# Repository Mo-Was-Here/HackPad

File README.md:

# 🚀 My Custom 3-Key Hackpad

> ⚠️ **Development Note:** The current 3D enclosure base file (`Top.STL`) is an initial layout draft to fulfill the folder architecture requirements. It is not currently matched to the exact final physical dimensions of the routed PCB and will be updated with precise mechanical alignments before final hardware fabrication.

A custom 3-key mechanical macro keypad featuring an integrated rotary encoder dial and individually addressable RGB backlight LEDs. The entire hardware framework is driven by a Seeed Studio XIAO RP2040 microcontroller and runs on the Python-based KMK keyboard firmware framework.

---

## 📐 Project Structure

This repository contains all source and manufacturing files required to build this project, organized according to Hack Club's shipping guidelines:
* `/CAD` - Contains the structural 3D design file (Top.STL) for the switch plate enclosure.
* `/PCB` - Contains the editable KiCad project, schematic, and board layout files.
* `/firmware` - Contains the core KMK configuration script (main.py).
* `/production` - Contains the manufacturing-ready gerbers.zip bundle and configuration assets.

---

## 📋 Bill of Materials (BOM)

| Component | Description | Qty | Part Source Link |
| :--- | :--- | :---: | :--- |
| **MCU** | Seeed Studio XIAO RP2040 Module | 1 | [Seeed Studio Official](https://seeedstudio.com) |
| **Switches** | Cherry MX Mechanical Keyswitches | 3 | [DigiKey Catalog](https://digikey.com) |
| **Encoder** | EC11 Rotary Encoder Dial with Built-in Switch | 1 | [Adafruit Supply](https://adafruit.com) |
| **LEDs** | SK6812MINI-E Individual Addressable RGB Components | 2 | [JLCPCB Parts Library](https://jlcpcb.com) |
| **Enclosure** | 1.5mm Custom 3D-Printed Switch Plate Base Shell | 1 | *Custom Manufactured STL File* |

---

## 🛠️ Pinout Mapping Reference

*   **SW1 (Key 1)** $\rightarrow$ GPIO Pin 11 (`board.D10`)
*   **SW2 (Key 2)** $\rightarrow$ GPIO Pin 10 (`board.D9`)
*   **SW3 (Key 3)** $\rightarrow$ GPIO Pin 9 (`board.D8`)
*   **Rotary Encoder Pins** $\rightarrow$ A: Pin 1 (`board.D0`) / B: Pin 2 (`board.D1`) / Switch: Pin 3 (`board.D2`)
*   **NeoPixel Data Bus** $\rightarrow$ Pin 7 (`board.D6`)
*   **Common Rails** $\rightarrow$ Positive: `+3V3` / Negative Return Path: `GND`

---

## 💻 Firmware Setup Instructions
This board runs CircuitPython with the KMK framework library. To deploy:
1. Flash the Seeed Studio XIAO with the latest CircuitPython .UF2 payload.
2. Copy the `kmk` firmware directory onto the root directory of the microcontroller storage volume.
3. Move the provided `main.py` configuration script onto the board to instantly map keybinds and lighting profiles.

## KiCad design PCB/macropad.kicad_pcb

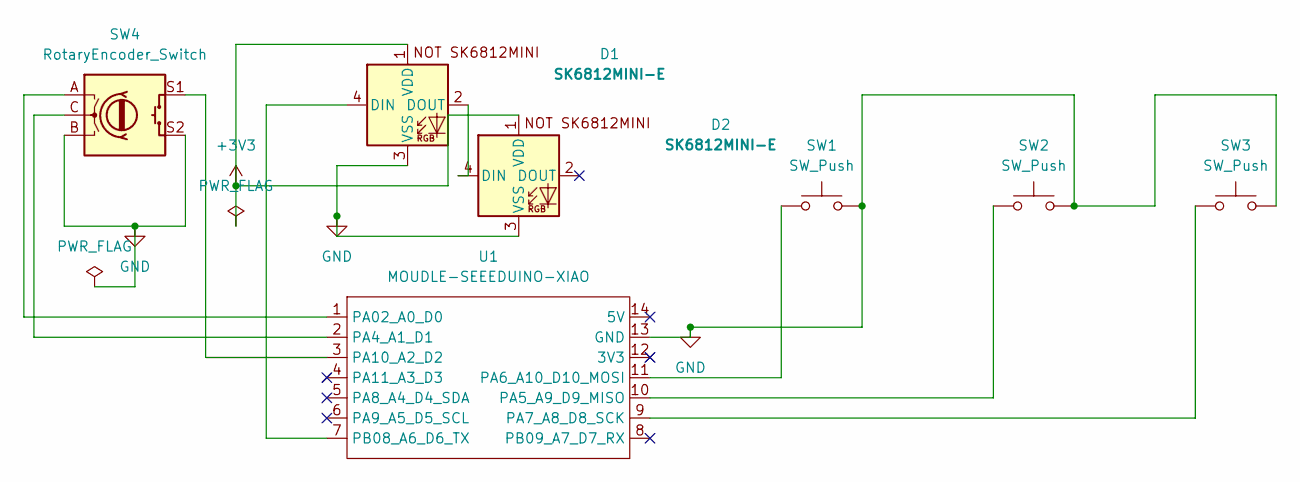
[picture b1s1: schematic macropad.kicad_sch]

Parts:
D1, D2: SK6812MINI-E; SK6812MINI-E_fixed
SW1, SW2, SW3: SW_Push; SW_Cherry_MX_1.25u_PCB
SW4: RotaryEncoder_Switch; RotaryEncoder_Alps_EC11E-Switch_Vertical_H20mm
U1: MOUDLE-SEEEDUINO-XIAO; MCU_Seeed_ESP32C3

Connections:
+3V3: D1.1 (VDD), D2.1 (VDD)
GND: D1.3 (VSS), D2.3 (VSS), SW1.2, SW2.2, SW3.2, SW4.B, SW4.S2, U1.13 (GND)
unnamed: D1.4 (DIN), U1.7 (PB08_A6_D6_TX)
unnamed: D1.2 (DOUT), D2.4 (DIN)
unnamed: SW4.A, U1.1 (PA02_A0_D0)
unnamed: SW4.C, U1.2 (PA4_A1_D1)
unnamed: SW2.1, U1.10 (PA5_A9_D9_MISO)
unnamed: SW1.1, U1.11 (PA6_A10_D10_MOSI)
unnamed: SW3.1, U1.9 (PA7_A8_D8_SCK)
unnamed: SW4.S1, U1.3 (PA10_A2_D2)

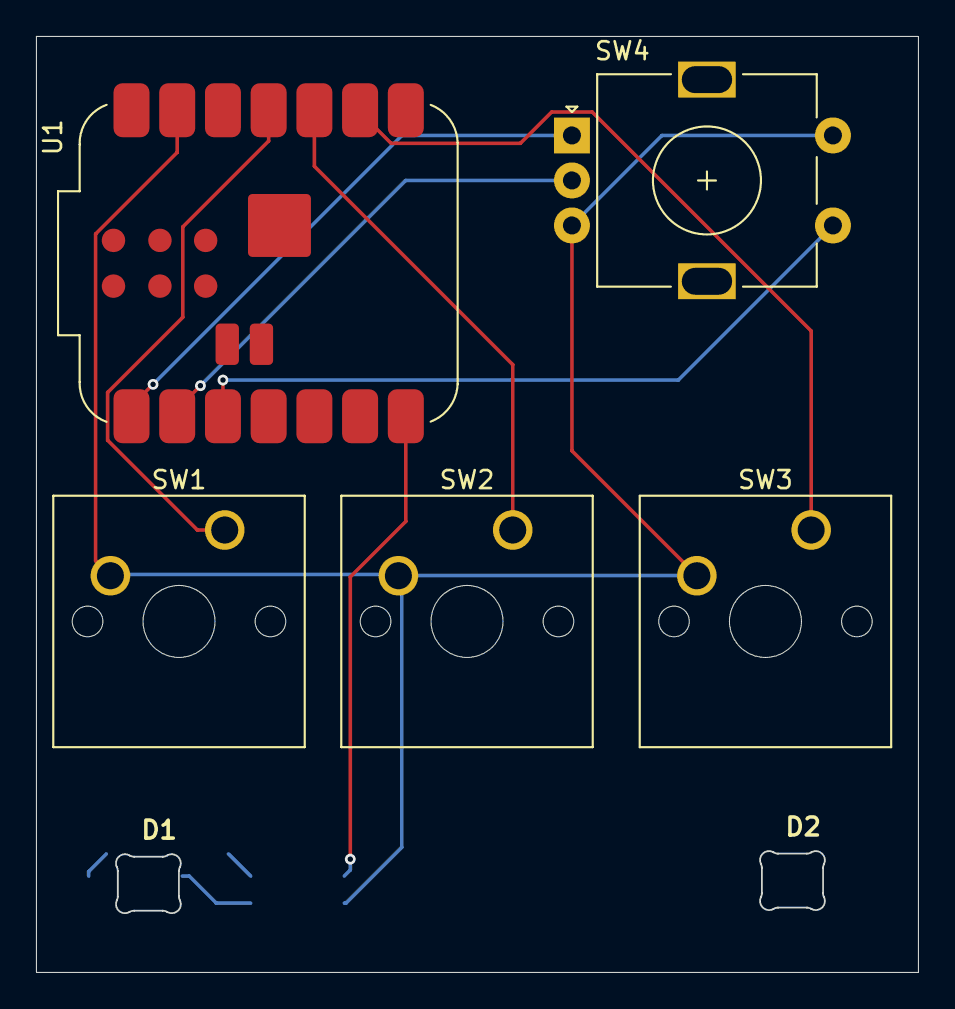
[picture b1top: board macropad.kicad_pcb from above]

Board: 2 copper layers, 49.0 x 52.0 mm, 7 parts (0 on the bottom side), 10 nets.

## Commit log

2026-06-03 README.md
